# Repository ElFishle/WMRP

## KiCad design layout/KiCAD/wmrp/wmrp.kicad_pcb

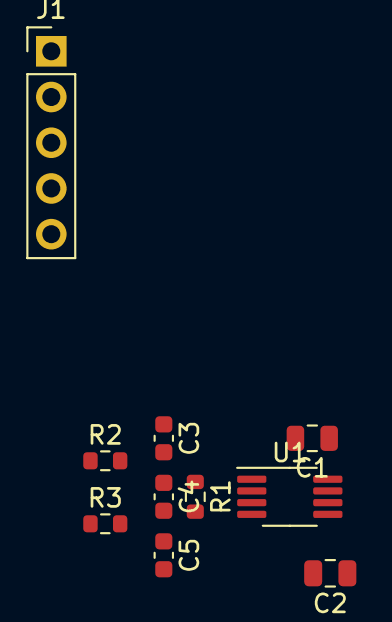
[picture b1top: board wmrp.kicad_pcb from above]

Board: 2 copper layers, 10 parts (0 on the bottom side), 9 nets, no tracks yet.

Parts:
C1, C2: 100nF; C_0805_2012Metric
C3, C5: 1nF; C_0603_1608Metric
C4: 22nF; C_0603_1608Metric
J1: DIN-5; PinHeader_1x05_P2.54mm_Vertical
R1: 1k; R_0603_1608Metric
R2, R3: 22k; R_0603_1608Metric
U1: AD8236; MSOP-8_3x3mm_P0.65mm

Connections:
+5V: C1.1, U1.8 (Vs+)
-5V: C2.1, U1.5 (Vs-)
/SENSOR-: J1.3, R2.1
/TIP_SENSOR+: J1.4, R3.1
GND: C1.2, C2.2, C3.1, C5.2, U1.6 (Ref)
unnamed: R1.1, U1.2 (Rg)
unnamed: R1.2, U1.3 (Rg)
unnamed: C3.2, C4.1, R2.2, U1.1 (-)
unnamed: C4.2, C5.1, R3.2, U1.4 (+)

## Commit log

2019-07-11 Some clarification about calculations
2019-07-11 Started KiCAD schematic
2022-12-20 Convert project to KiCAD 6
2022-12-20 Unpacked eagle project for editing
2022-12-20 Make proper project file
2022-12-20 First try to use instrumentation amplifier for thermocouple reading
